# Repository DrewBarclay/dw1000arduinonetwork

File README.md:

# dw1000arduinonetwork
For our computer engineering capstone project. Takes a number of DW1000s hooked up to Arduinos and has them transmit their range information to each other and to serial interfaces. For use with our other projects.

Code is intended to run on an Arduino Pro Mini 3.3V. See https://github.com/thotro/arduino-dw1000 for the core code used, as well as the final report at https://github.com/DrewBarclay/ARLocationTracking for more information.

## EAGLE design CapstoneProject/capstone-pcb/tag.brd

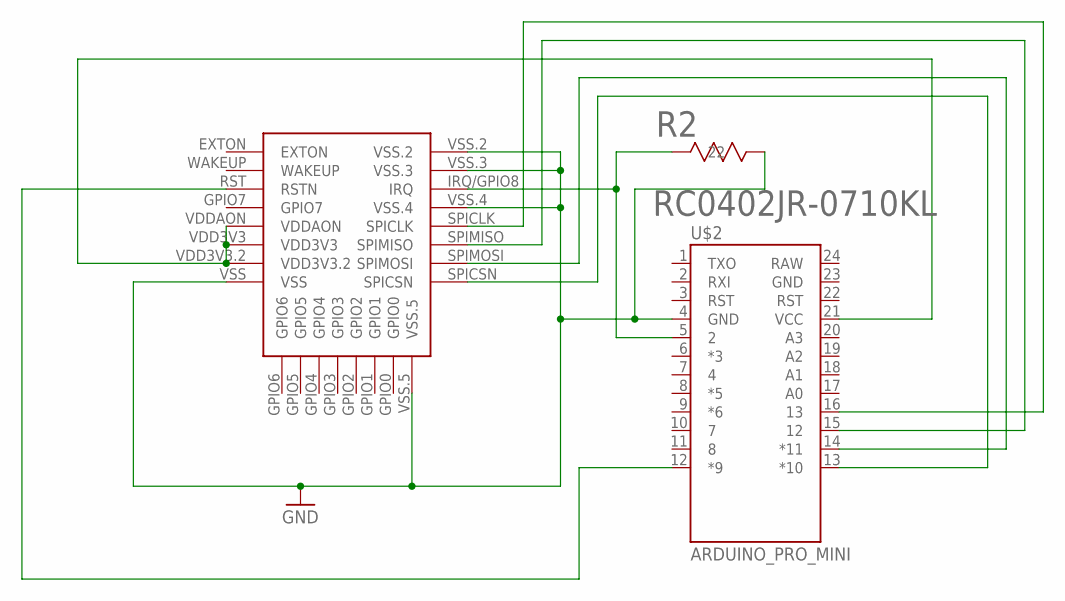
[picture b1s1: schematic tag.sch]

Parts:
R2: RC0402JR-0710KL; RC0402N
U$1: DWM1000
U$2: ARDUINO_PRO_MINI

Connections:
GND: R2.1 (11), U$1.VSS, U$1.VSS.2, U$1.VSS.3, U$1.VSS.4, U$1.VSS.5, U$2.4 (GND)
unnamed: U$1.VDD3V3, U$1.VDD3V3.2, U$1.VDDAON, U$2.21 (VCC)
unnamed: R2.2 (22), U$1.IRQ/GPIO8 (IRQ), U$2.5 (2)
unnamed: U$1.RST (RSTN), U$2.12 (*9)
unnamed: U$1.SPIMISO, U$2.15 (12)
unnamed: U$1.SPICLK, U$2.16 (13)
unnamed: U$1.SPIMOSI, U$2.14 (*11)
unnamed: U$1.SPICSN, U$2.13 (*10)

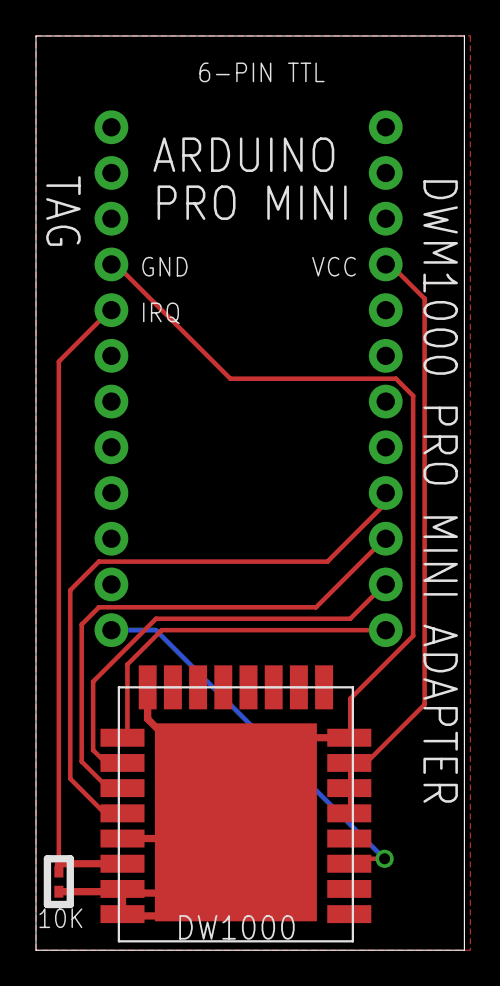
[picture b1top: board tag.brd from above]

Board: 2 copper layers, 23.8 x 50.8 mm, 3 parts (0 on the bottom side), 8 nets.

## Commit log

2017-01-20 Initial commit.
2017-01-20 Added folder
2017-01-20 Debugging.
2017-01-20 Fixed division by zero error?
2017-01-20 Attempt at a fix for computeRange crashing the system.
2017-01-20 More error handling.
2017-02-01 Updated to use a cached range. Maybe it'll fix the bugs.
2017-02-01 Moved away from array of timestamps due to missed transmissions.
2017-02-03 Reworking project to be more robust; changing protocol to have a transmission counter.
2017-02-04 Refactored a little, cleaned up the code, beginnings of the measures to make the program more robust.
2017-02-10 First working(?) version after refactor.
2017-02-10 Hopefully fixing range bugs (as I was setting the delay outside a transmission set)
2017-02-10 Working version with range (had to set delay to 3ms, 1ms too small).
2017-02-10 Removed a lot of debugging stuff.
2017-02-13 Figured out equation for proper delay.
2017-02-13 Working version of the code (handles at least 5 devices; trying 7 later).
2017-03-09 Code reworked to time-share system, but it's not working well. Reworking to code to be more elegant later.
2017-03-13 Working time-share system.
2017-03-13 Lowered preamble length; appears to be working well.
2017-03-14 Added EAGLE schematic.
2017-03-17 Added our tweaked version of thotro's library.
2017-03-17 Updated with dwm library.
2017-03-17 Modified thotro's library.
2017-03-17 Tweaked library.
2017-03-17 Tweaked library fixes.
2017-03-20 Latest code with calibrations and baud rate reduced.
2017-03-20 Optimized transfer speed. Apparently this optimization was lost.
2017-03-20 Latest.
2017-03-20 Fixed use of Serial.println causing excessive slowdown by changing to String concat.
2017-03-31 1 million baud rate seems to work well.
2017-04-05 Updated code to allow devices to disconnect and reconnect (devices are dropped after a number of missed transmissions). Improved efficiency of Serial.print via reserving memory in a global String.
2017-04-06 Latest version. Mostly working and optimized?

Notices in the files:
parts and their libraries:
SparkFun-Boards: Licensing: Creative Commons ShareAlike 4.0 International - https://creativecommons.org/licenses/by-sa/4.0
COPYRIGHT: Copyright C 2015 Accelerated Designs. All rights reserved
